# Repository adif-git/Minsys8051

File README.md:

# Minsys8051

This is minimum system board PCB Design for 8051 Microcontroller. EAGLE Software is used for designing this PCB.

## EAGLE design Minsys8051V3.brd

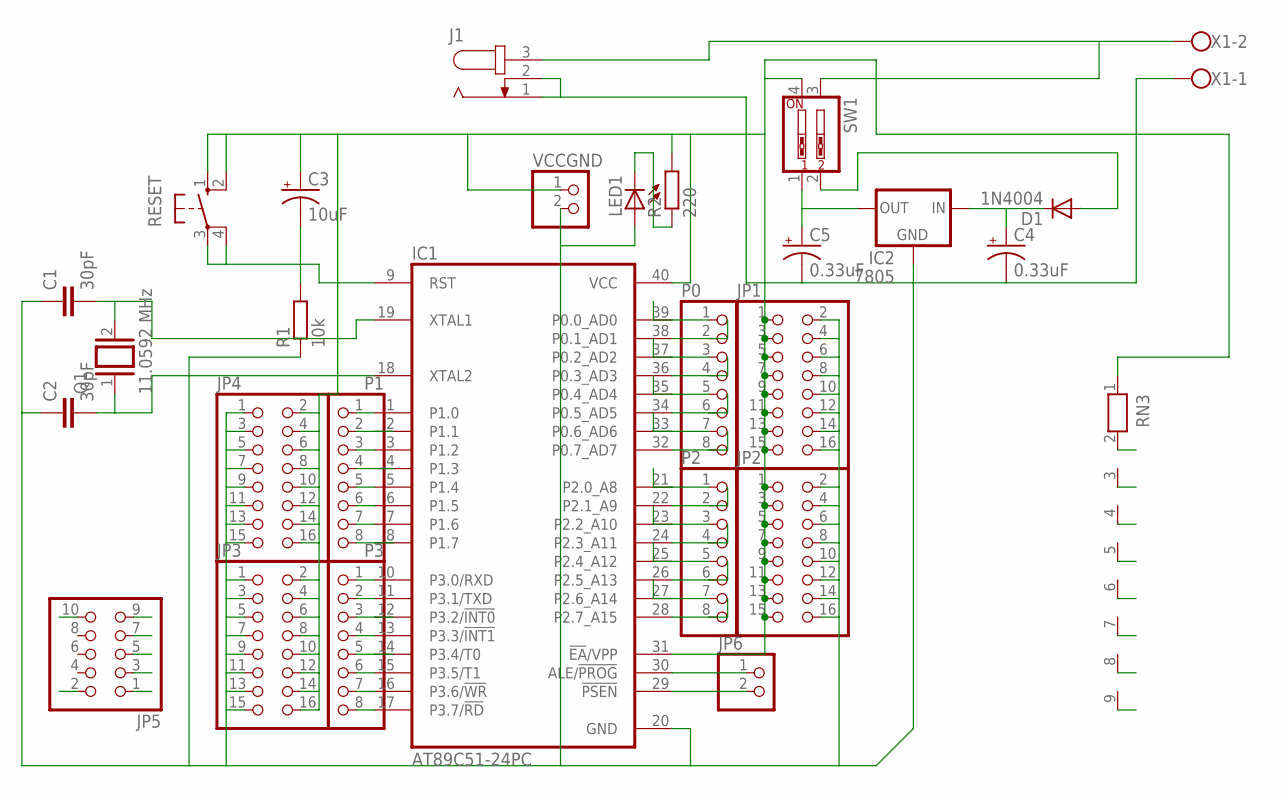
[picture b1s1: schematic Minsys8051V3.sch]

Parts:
C1, C2: 30pF; C025-025X050
C3: 10uF; TT5D6
C4, C5: 0.33uF; TT5D6
D1: 1N4004; DO41-10
IC1: AT89C51-24PC; DIL40
IC2: 7805; 78XXS
J1: JACK-PLUG1; SPC4078
JP1, JP2, JP3, JP4: PINHD-2X8; 2X08
JP5: PINHD-2X5; 2X05
JP6: PINHD-1X2; 1X02
LED1: LED_ELD260; LED_LD260
P0, P1, P2, P3: PINHD-1X8; 1X08
Q1: 11.0592 MHz; QS
R1: 10k; 0207/10
R2: 220; 0207/10
RESET: 10-XX; B3F-10XX
RN3: RN08; RN-9
SW1: SW_DIP-2; EDG-02
VCCGND: PINHD-1X2; 1X02
X1: W237-102

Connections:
GND: C1.1, C2.1, C4.-, C5.-, IC1.20 (GND), IC2.GND, J1.1, J1.2, JP1.2, JP1.4, JP1.6, JP1.8, JP1.10, JP1.12, JP1.14, JP1.16, JP2.2, JP2.4, JP2.6, JP2.8, JP2.10, JP2.12, JP2.14, JP2.16, JP3.1, JP3.3, JP3.5, JP3.7, JP3.9, JP3.11, JP3.13, JP3.15, JP4.1, JP4.3, JP4.5, JP4.7, JP4.9, JP4.11, JP4.13, JP4.15, JP5.2, LED1.A, R1.1, VCCGND.2, X1.1
MISO: IC1.7 (P1.6), JP5.1, P1.7
MOSI: IC1.6 (P1.5), JP5.9, P1.6
unnamed: IC1.30 (ALE/!PROG), JP6.1
unnamed: LED1.K (C), R2.1
unnamed: C1.2, IC1.19 (XTAL1), Q1.2
unnamed: C2.2, IC1.18 (XTAL2), Q1.1
unnamed: IC1.29 (!PSEN), JP6.2
unnamed: J1.3, SW1.3, X1.2
unnamed: D1.A, SW1.2
unnamed: C5.+, IC2.OUT, SW1.1
unnamed: C4.+, D1.C, IC2.IN
P00: IC1.39 (P0.0_AD0), P0.1, RN3.2
P01: IC1.38 (P0.1_AD1), P0.2, RN3.3
P02: IC1.37 (P0.2_AD2), P0.3, RN3.4
P03: IC1.36 (P0.3_AD3), P0.4, RN3.5
P04: IC1.35 (P0.4_AD4), P0.5, RN3.6
P05: IC1.34 (P0.5_AD5), P0.6, RN3.7
P06: IC1.33 (P0.6_AD6), P0.7, RN3.8
P07: IC1.32 (P0.7_AD7), P0.8, RN3.9
P10: IC1.1 (P1.0), P1.1
P11: IC1.2 (P1.1), P1.2
P12: IC1.3 (P1.2), P1.3
P13: IC1.4 (P1.3), P1.4
P14: IC1.5 (P1.4), P1.5
P20: IC1.21 (P2.0_A8), P2.1
P21: IC1.22 (P2.1_A9), P2.2
P22: IC1.23 (P2.2_A10), P2.3
P23: IC1.24 (P2.3_A11), P2.4
P24: IC1.25 (P2.4_A12), P2.5
P25: IC1.26 (P2.5_A13), P2.6
P26: IC1.27 (P2.6_A14), P2.7
P27: IC1.28 (P2.7_A15), P2.8
P30: IC1.10 (P3.0/RXD), P3.1
P31: IC1.11 (P3.1/TXD), P3.2
P32: IC1.12 (P3.2/!INT0), P3.3
P33: IC1.13 (P3.3/!INT1), P3.4
P34: IC1.14 (P3.4/T0), P3.5
P35: IC1.15 (P3.5/T1), P3.6
P36: IC1.16 (P3.6/!WR), P3.7
P37: IC1.17 (P3.7/!RD), P3.8
RST: C3.-, IC1.9 (RST), JP5.5, R1.2, RESET.3, RESET.4 (P1)
SCK: IC1.8 (P1.7), JP5.3, P1.8
VCC: C3.+, IC1.31 (!EA!/VPP), IC1.40 (VCC), JP1.1, JP1.3, JP1.5, JP1.7, JP1.9, JP1.11, JP1.13, JP1.15, JP2.1, JP2.3, JP2.5, JP2.7, JP2.9, JP2.11, JP2.13, JP2.15, JP3.2, JP3.4, JP3.6, JP3.8, JP3.10, JP3.12, JP3.14, JP3.16, JP4.2, JP4.4, JP4.6, JP4.8, JP4.10, JP4.12, JP4.14, JP4.16, JP5.10, R2.2, RESET.1 (S), RESET.2 (S1), RN3.1, SW1.4, VCCGND.1

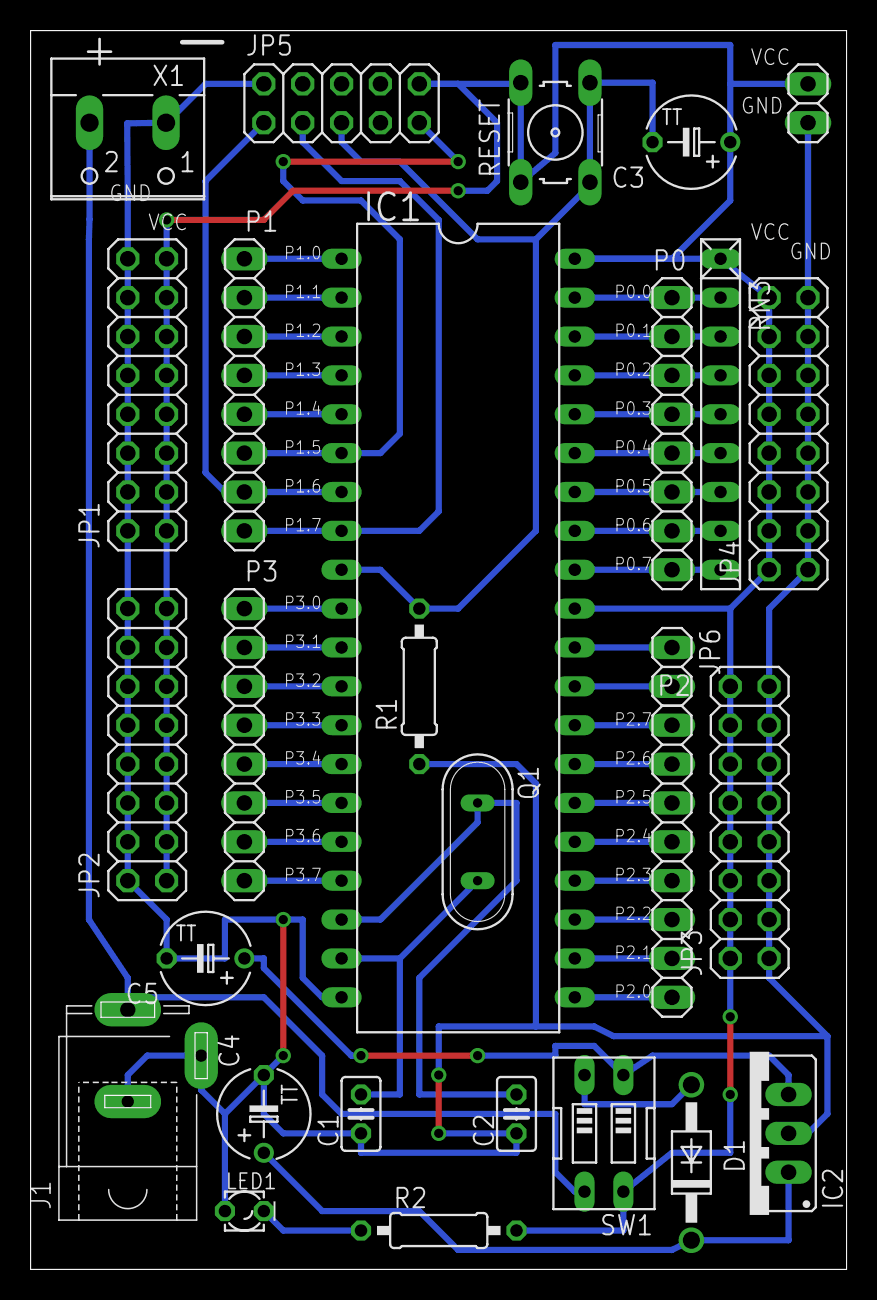
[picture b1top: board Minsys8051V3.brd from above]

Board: 2 copper layers, 53.3 x 81.0 mm, 28 parts (0 on the bottom side), 44 nets.

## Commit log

2020-04-24 Fix folder
